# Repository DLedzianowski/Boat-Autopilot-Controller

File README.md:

# Boat-Autopilot-Controller
PCB for a small boat autopilot system. Collects sensor data and drives actuators to maintain set course/position.

## Main Features
- STM32WB55 – main MCU with BLE
- MAX-M10S – GNSS positioning
- TMC2208 – stepper motor driver
- LIS3MDL – magnetometer (compass)
- AS5600 connector – absolute encoder input
- DC motor controller connector

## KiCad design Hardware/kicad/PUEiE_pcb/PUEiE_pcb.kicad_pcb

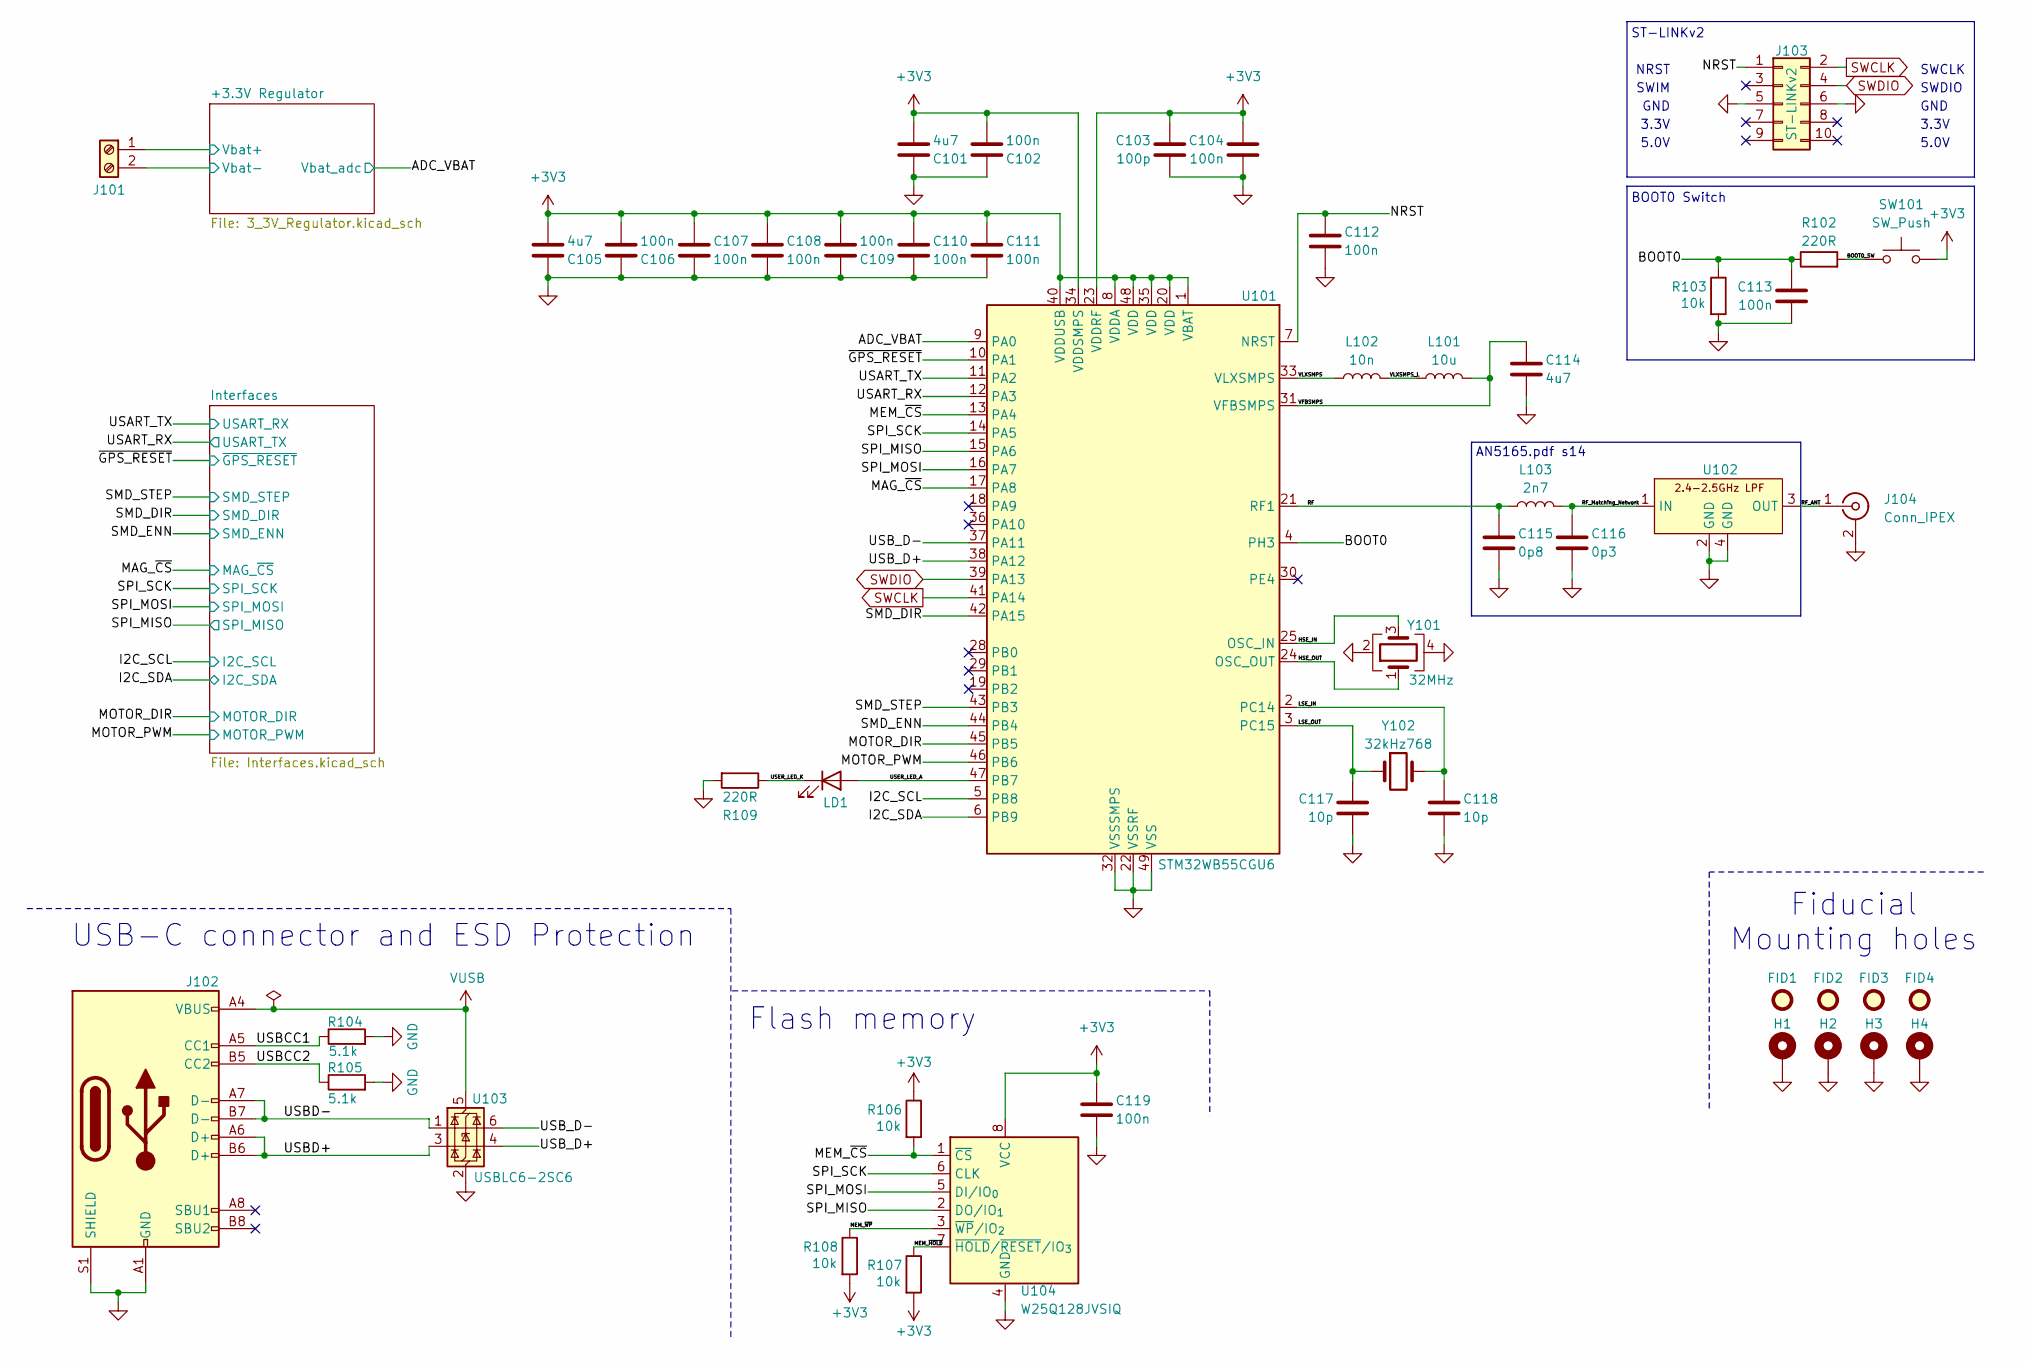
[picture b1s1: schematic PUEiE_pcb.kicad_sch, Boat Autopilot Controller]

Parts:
C101, C105, C114: 4u7; C_0805_2012Metric; MFR Part CL21A475KAQNNNE
C102, C104, C106, C107, C108, C109, C110, C111, C112, C113, C119: 100n; C_0805_2012Metric; MFR Part CL21B104KCFNNNE
C103: 100p; C_0805_2012Metric; MFR Part CL21C101JBANNNC
C115: 0p8; C_0402_1005Metric; MFR Part GRM1555C1HR80BA01D
C116: 0p3; C_0402_1005Metric; MFR Part GRM1555C1HR30WA01D
C117, C118: 10p; C_0603_1608Metric; MFR Part CL10C100JB8NNNC
FID1, FID2, FID3, FID4: Fiducial; Fiducial_1mm_Mask2mm
H1, H2, H3, H4: MountingHole_Pad; MountingHole_3.2mm_M3_Pad
J101: Screw_Terminal_01x02; TerminalBlock_Phoenix_PT-1,5-2-3.5-H_1x02_P3.50mm_Horizontal; MFR Part PRT-08084
J102: USB_C_Receptacle_USB2.0_16P; USB_C_Receptacle_GCT_USB4105-xx-A_16P_TopMnt_Horizontal; MFR Part USB4105-GF-A-060
J103: ST-LINKv2; PinHeader_2x05_P2.54mm_Vertical; MFR Part HX JN1.27-2x5P ZZ H4.9
J104: Conn_IPEX; IPEX Male; MFR Part BWIPX-1-001E
L101: 10u; L_0603_1608Metric; MFR Part SDFL1608S100KTF
L102: 10n; L_0402_1005Metric; MFR Part LQG15WZ10NJ02D
L103: 2n7; L_0402_1005Metric; MFR Part LQG15HS2N7S02D
LD1: LD1; LED_0805_2012Metric; MFR Part NCD0805B2
R102, R109: 220R; R_0805_2012Metric; MFR Part 0805W8F2200T5E
R103, R106, R107, R108: 10k; R_0805_2012Metric; MFR Part 0805W8F1002T5E
R104, R105: 5.1k; R_0805_2012Metric; MFR Part 0805W8F5101T5E
SW101: SW_Push; SW_2pin_5.5x2.0mm; MFR Part TS-1088-AR02016
U101: STM32WB55CGU6; QFN-48-1EP_7x7mm_P0.5mm_EP5.6x5.6mm_ThermalVias; MFR Part STM32WB55CGU6
U102: DLF162500LT-5028A1; MFR Part DLF162500LT-5028A1
U103: USBLC6-2SC6; SOT-23-6; MFR Part USBLC6-2SC6
U104: W25Q128JVSIQ; SOIC-8_5.3x5.3mm_P1.27mm; MFR Part W25Q128JVSIQ
Y101: 32MHz; Crystal_SMD_2016-4Pin_2.0x1.6mm; MFR Part NX2016SA-32MHZ-STD-CZS-5
Y102: 32kHz768; Crystal_SMD_2012-2Pin_2.0x1.2mm; MFR Part NX2012SA 32.768KHZ STD-MUB-1

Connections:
+3V3: C101.2, C102.2, C103.1, C104.1, C105.2, C106.2, C107.1, C108.1, C109.2, C110.1, C111.1, C119.1, R106.1, R107.2, R108.2, SW101.2, U101.1 (VBAT), U101.8 (VDDA), U101.20 (VDD), U101.23 (VDDRF), U101.34 (VDDSMPS), U101.35 (VDD), U101.40 (VDDUSB), U101.48 (VDD), U104.8 (VCC); also elsewhere on the board
/+3.3V Regulator/Vbat+: J101.1; also elsewhere on the board
/ADC_VBAT: U101.9 (PA0); also elsewhere on the board
/BOOT0: C113.1, R102.1, R103.1, U101.4 (PH3)
/BOOT0_SW: R102.2, SW101.1
/HSE_IN: U101.25 (OSC_IN), Y101.3
/HSE_OUT: U101.24 (OSC_OUT), Y101.1
/I2C_SCL: U101.5 (PB8); also elsewhere on the board
/I2C_SDA: U101.6 (PB9); also elsewhere on the board
/LSE_IN: C118.1, U101.2 (PC14), Y102.2
/LSE_OUT: C117.1, U101.3 (PC15), Y102.1
/MAG_~CS: U101.17 (PA8); also elsewhere on the board
/MEM_~CS: R106.2, U101.13 (PA4), U104.1 (~CS)
/MEM_~HOLD: R107.1, U104.7 (~HOLD/~RESET/IO_{3})
/MEM_~WP: R108.1, U104.3 (~WP/IO_{2})
/MOTOR_DIR: U101.45 (PB5); also elsewhere on the board
/MOTOR_PWM: U101.46 (PB6); also elsewhere on the board
/NRST: C112.1, J103.1, U101.7 (NRST)
/RF: C115.1, L103.1, U101.21 (RF1)
/RF_ANT: J104.1 (In), U102.3 (OUT)
/RF_Matching_Network: C116.1, L103.2, U102.1 (IN)
/SMD_DIR: U101.42 (PA15); also elsewhere on the board
/SMD_ENN: U101.44 (PB4); also elsewhere on the board
/SMD_STEP: U101.43 (PB3); also elsewhere on the board
/SPI_MISO: U101.15 (PA6), U104.2 (DO/IO_{1}); also elsewhere on the board
/SPI_MOSI: U101.16 (PA7), U104.5 (DI/IO_{0}); also elsewhere on the board
/SPI_SCK: U101.14 (PA5), U104.6 (CLK); also elsewhere on the board
/USART_RX: U101.12 (PA3); also elsewhere on the board
/USART_TX: U101.11 (PA2); also elsewhere on the board
/USBCC1: J102.A5 (CC1), R104.1
/USBCC2: J102.B5 (CC2), R105.1
/USBD+: J102.A6 (D+), J102.B6 (D+), U103.3 (I/O2)
/USBD-: J102.A7 (D-), J102.B7 (D-), U103.1 (I/O1)
/USB_D+: U101.38 (PA12), U103.4 (I/O2)
/USB_D-: U101.37 (PA11), U103.6 (I/O1)
/USER_LED_A: LD1.2 (A), U101.47 (PB7)
/USER_LED_K: LD1.1 (K), R109.1
/VFBSMPS: C114.1, L101.2, U101.31 (VFBSMPS)
/VLXSMPS: L102.1, U101.33 (VLXSMPS)
/VLXSMPS_L: L101.1, L102.2
/~GPS_RESET: U101.10 (PA1); also elsewhere on the board
GND: C101.1, C102.1, C103.2, C104.2, C105.1, C106.1, C107.2, C108.2, C109.1, C110.2, C111.2, C112.2, C113.2, C114.2, C115.2, C116.2, C117.2, C118.2, C119.2, H1.1, H2.1, H3.1, H4.1, J101.2, J102.A1 (GND), J102.A12 (GND), J102.B1 (GND), J102.B12 (GND), J102.S1 (SHIELD), J103.5, J103.6, J104.2 (Ext), R103.2, R104.2, R105.2, R109.2, U101.22 (VSSRF), U101.32 (VSSSMPS), U101.49 (VSS), U102.2 (GND), U102.4 (GND), U103.2 (GND), U104.4 (GND), Y101.2, Y101.4; also elsewhere on the board
SWCLK: J103.2, U101.41 (PA14)
SWDIO: J103.4, U101.39 (PA13)
VUSB: J102.A4 (VBUS), J102.A9 (VBUS), J102.B4 (VBUS), J102.B9 (VBUS), U103.5 (VBUS); also elsewhere on the board

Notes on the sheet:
AN5165.pdf s14
5.0V
BOOT0 Switch
GND
USB-C connector and ESD Protection
3.3V
SWDIO
SWCLK
ST-LINKv2
Fiducial Mounting holes
SWIM
Flash memory
NRST

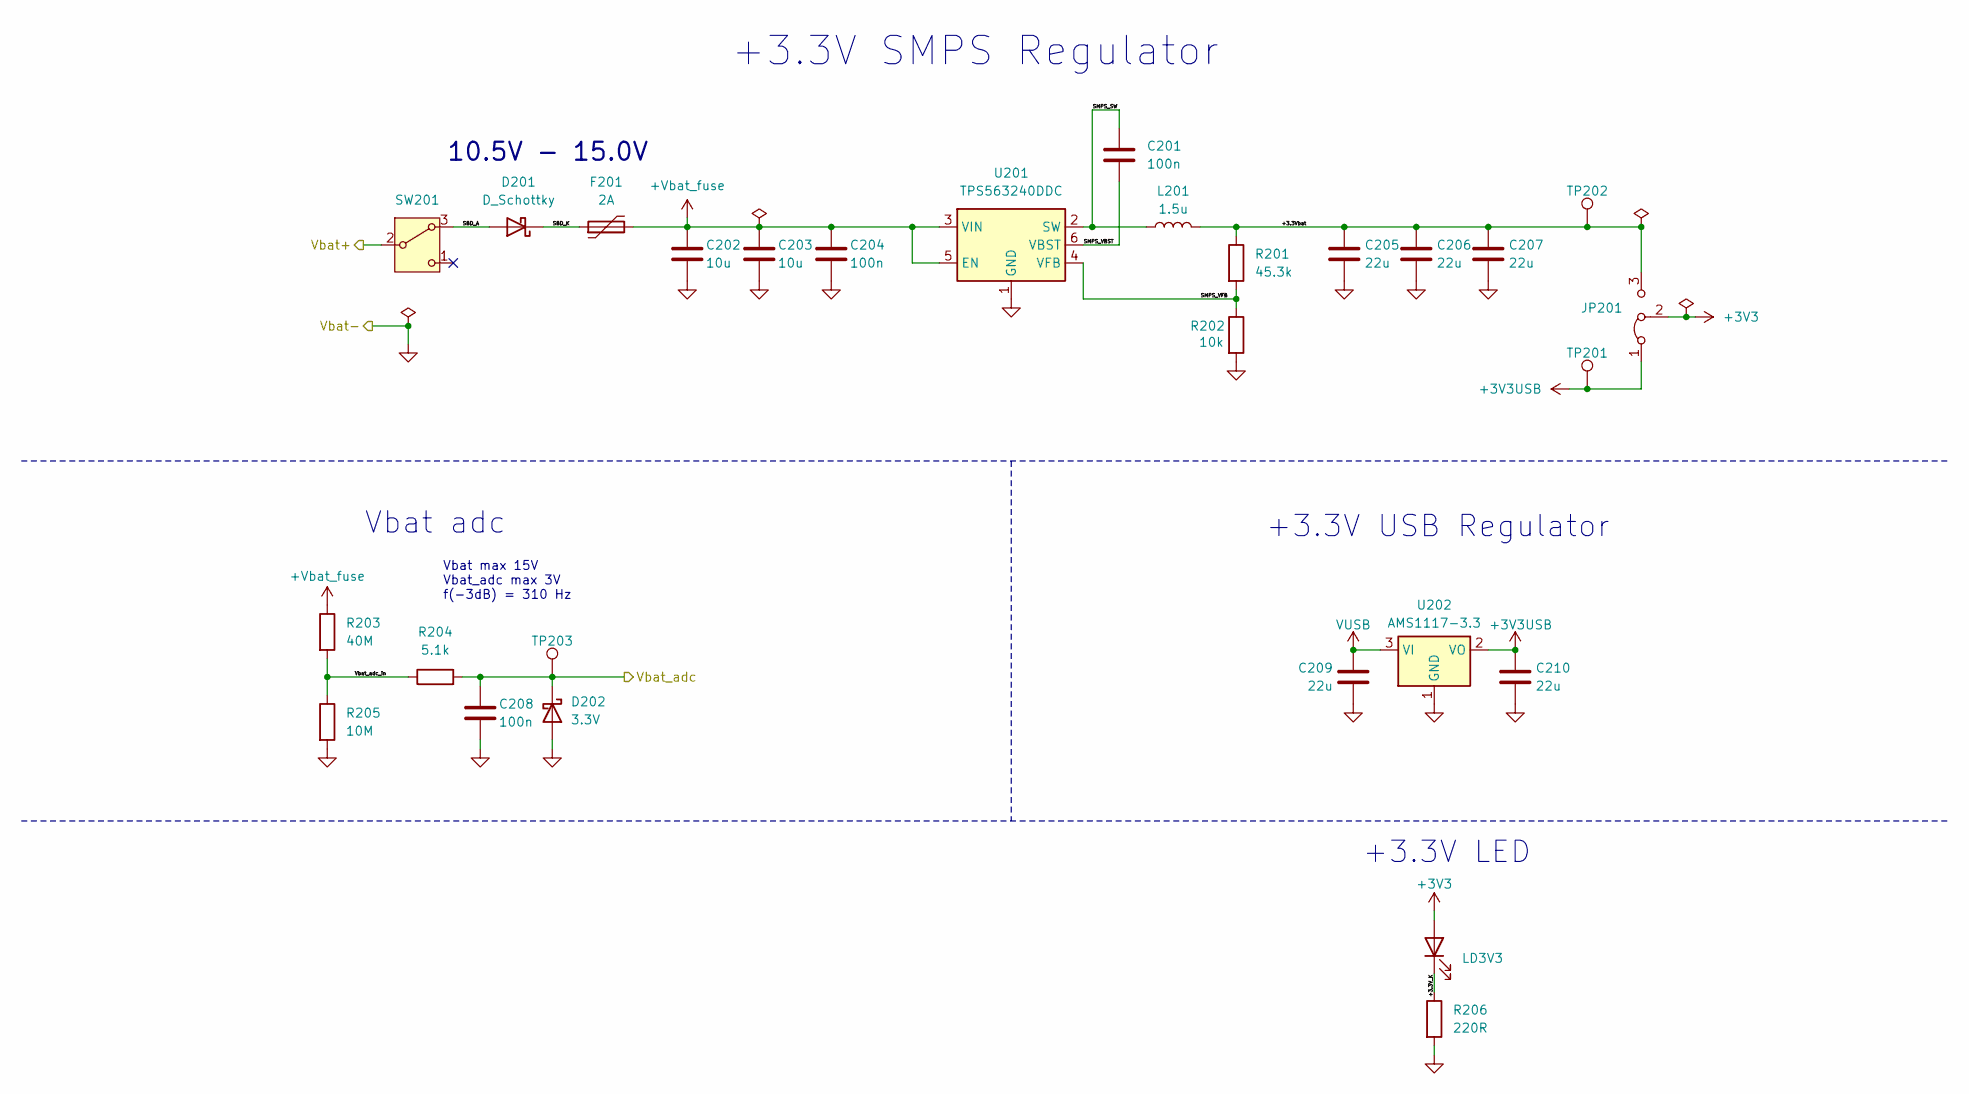
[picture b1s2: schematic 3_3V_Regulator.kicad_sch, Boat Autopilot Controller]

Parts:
C201: 100n; C_0603_1608Metric; MFR Part EMK107B7104KA-T
C202, C203: 10u; C_0805_2012Metric; MFR Part GRM21BR61E106MA73L
C204, C208: 100n; C_0805_2012Metric; MFR Part CL21B104KCFNNNE
C205, C206, C207, C209, C210: 22u; C_0603_1608Metric; MFR Part GRM188R60J226MEA0D
D201: D_Schottky; D_SMA; MFR Part SS34
D202: 3.3V; D_SOD-323; MFR Part MMSZ5226BS-7-F
F201: 2A; Fuseholder_Clip-5x20mm_Littelfuse_111_Inline_P20.00x5.00mm_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; MFR Part 5x20 环保 保险管夹/座
JP201: Jumper_3_Bridged12; PinHeader_1x03_P2.54mm_Vertical
L201: 1.5u; L_Sunlord_MWSA1005S; MFR Part 104CDMCCDS-1R5MC
LD3V3: +3.3V; LED_0805_2012Metric; MFR Part NCD0805R1
R201: 45.3k; R_0805_2012Metric; MFR Part 0805W8F4532T5E
R202: 10k; R_0805_2012Metric; MFR Part 0805W8F1002T5E
R203: 40M; R_0805_2012Metric; MFR Part RH73H2A40MKTN
R204: 5.1k; R_0805_2012Metric; MFR Part 0805W8F5101T5E
R205: 10M; R_0805_2012Metric; MFR Part 0805W8F1005T5E
R206: 220R; R_0805_2012Metric; MFR Part 0805W8F2200T5E
SW201: SW_Nidec_CAS-120A1; PinHeader_1x03_P2.54mm_Vertical; MFR Part TS01CBE
TP201, TP202, TP203: TestPoint; TestPoint_Pad_D2.0mm
U201: TPS563240DDC; SOT-23-6; MFR Part TPS563240DDCR
U202: AMS1117-3.3; SOT-223-3_TabPin2; MFR Part AMS1117-3.3

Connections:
+3V3: JP201.2 (C), LD3V3.2 (A); also elsewhere on the board
+3V3USB: C210.1, JP201.1 (A), TP201.1, U202.2 (VO)
+Vbat_fuse: C202.1, C203.1, C204.1, F201.2, R203.1, U201.3 (VIN), U201.5 (EN); also elsewhere on the board
/+3.3V Regulator/+3.3V_K: LD3V3.1 (K), R206.1
/+3.3V Regulator/+3.3Vbat: C205.1, C206.1, C207.1, JP201.3 (B), L201.2, R201.1, TP202.1
/+3.3V Regulator/SBD_A: D201.2 (A), SW201.3 (A)
/+3.3V Regulator/SBD_K: D201.1 (K), F201.1
/+3.3V Regulator/SMPS_SW: C201.1, L201.1, U201.2 (SW)
/+3.3V Regulator/SMPS_VBST: C201.2, U201.6 (VBST)
/+3.3V Regulator/SMPS_VFB: R201.2, R202.1, U201.4 (VFB)
/+3.3V Regulator/Vbat+: SW201.2 (B); also elsewhere on the board
/+3.3V Regulator/Vbat_adc_in: R203.2, R204.1, R205.1
/ADC_VBAT: C208.1, D202.1 (K), R204.2, TP203.1; also elsewhere on the board
GND: C202.2, C203.2, C204.2, C205.2, C206.2, C207.2, C208.2, C209.2, C210.2, D202.2 (A), R202.2, R205.2, R206.2, U201.1 (GND), U202.1 (GND); also elsewhere on the board
VUSB: C209.1, U202.3 (VI); also elsewhere on the board

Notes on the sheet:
Vbat adc
+3.3V SMPS Regulator
Vbat max 15V Vbat_adc max 3V f(-3dB) = 310 Hz
+3.3V USB Regulator
+3.3V LED
10.5V - 15.0V

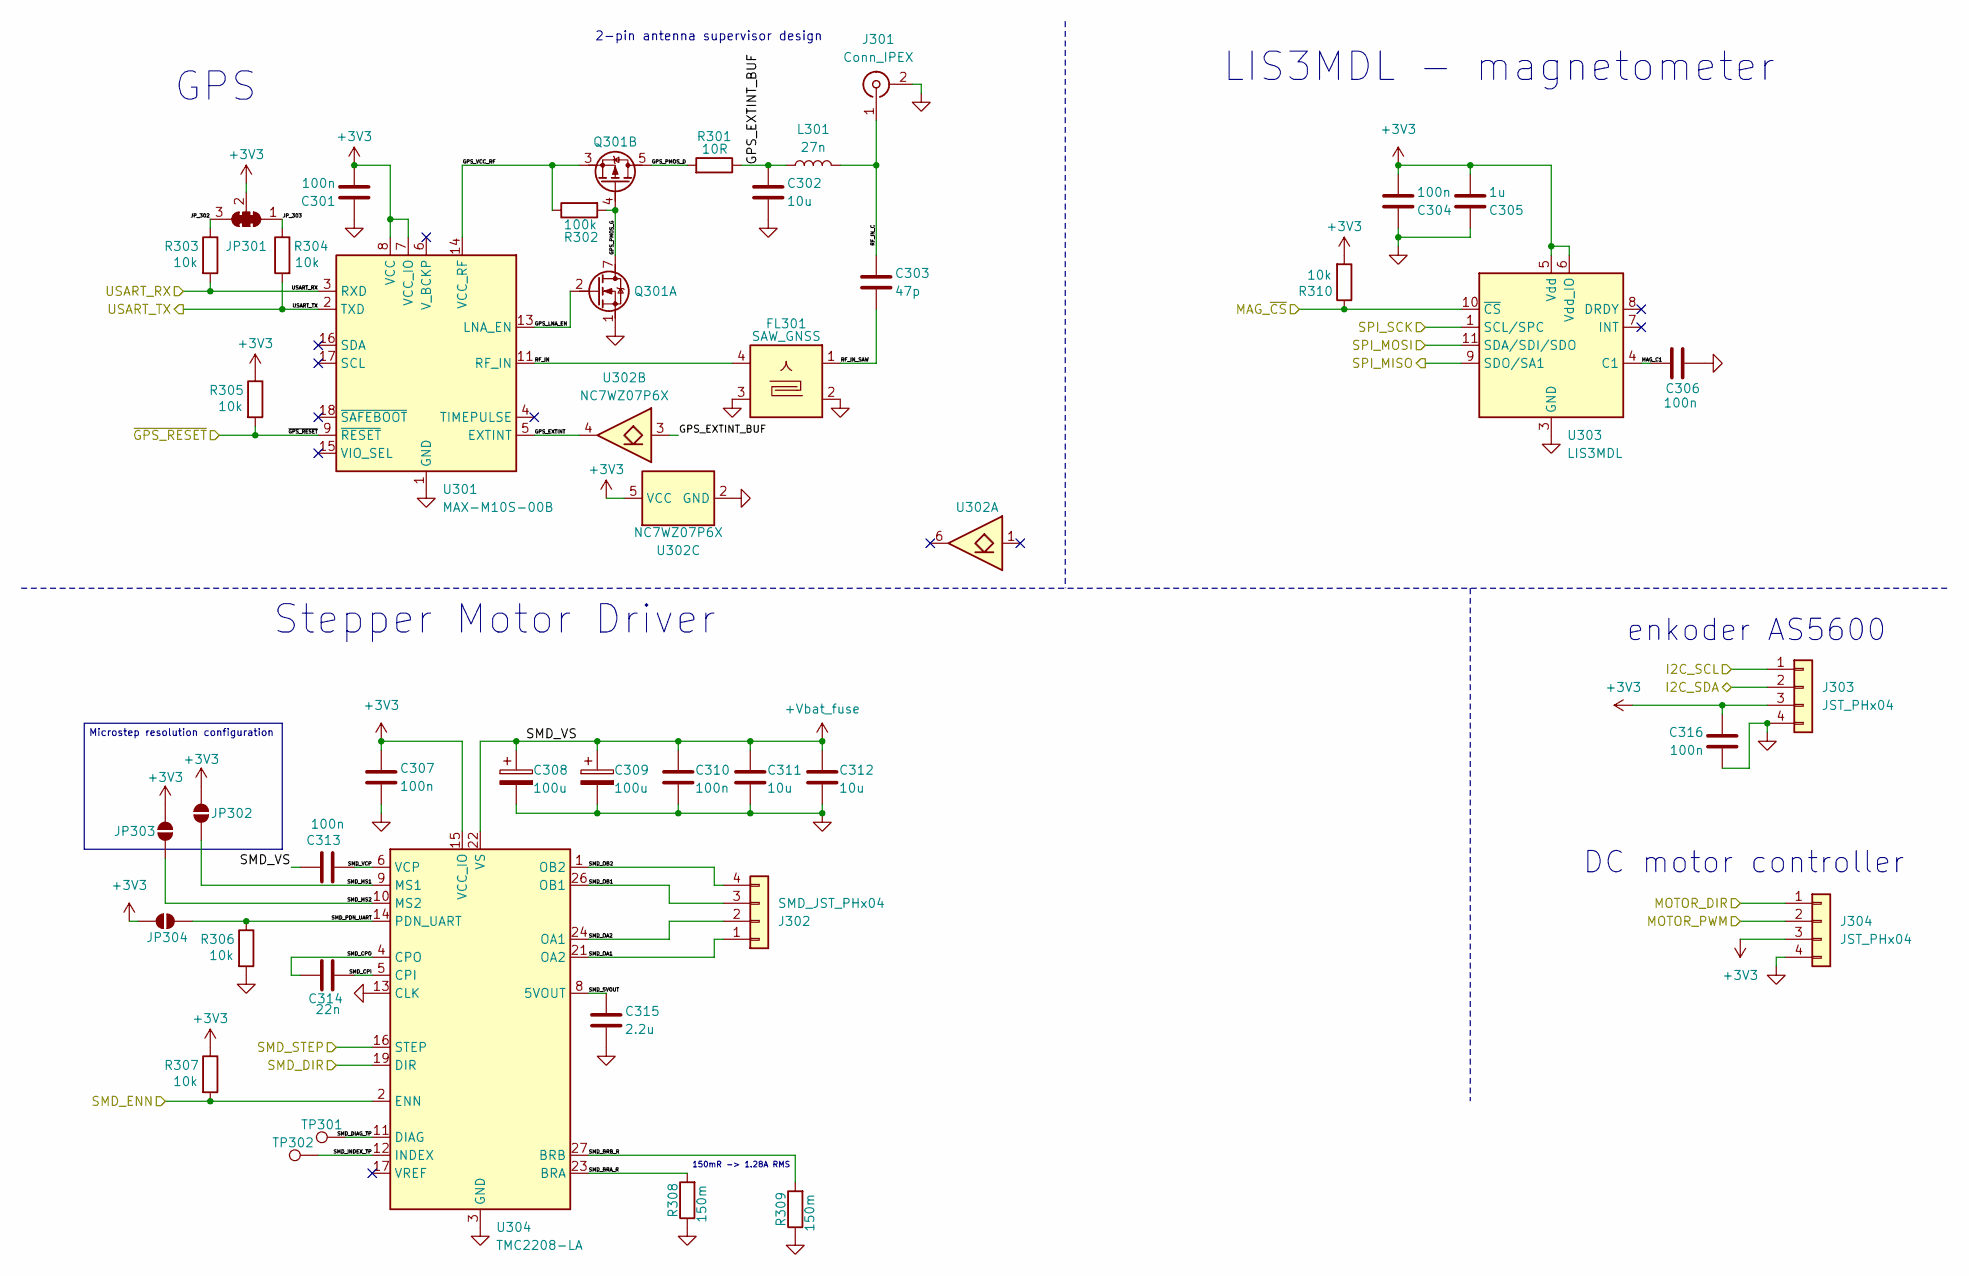
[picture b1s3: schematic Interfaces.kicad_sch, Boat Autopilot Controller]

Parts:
C301, C304, C306, C307, C310, C313, C316: 100n; C_0805_2012Metric; MFR Part CL21B104KCFNNNE
C302: 10u; C_0805_2012Metric; MFR Part CL21B103KBANNNC
C303: 47p; C_0805_2012Metric; MFR Part C2012C0G1H470JT000N
C305: 1u; C_0805_2012Metric; MFR Part CL21B105KBFNNNE
C308, C309: 100u; CP_Elec_6.3x7.7; MFR Part RVT1E101M0607
C311, C312: 10u; C_1206_3216Metric; MFR Part CL31A106KBHNNNE
C314: 22n; C_0805_2012Metric; MFR Part CL21B104KCFNNNE
C315: 2.2u; C_0805_2012Metric; MFR Part CL21A225KBQNNNE
FL301: SAW_GNSS; Filter_1109-5_1.1x0.9mm; MFR Part SAFFB1G56KB0F0AR1X
J301: Conn_IPEX; IPEX Male; MFR Part BWIPX-1-001E
J302: SMD_JST_PHx04; JST_XH_S4B-XH-A_1x04_P2.50mm_Horizontal; MFR Part S4B-XH-A-1
J303, J304: JST_PHx04; JST_XH_S4B-XH-A_1x04_P2.50mm_Horizontal; MFR Part S4B-XH-A-1
JP301: SolderJumper_3_Bridged123; SolderJumper-3_P2.0mm_Open_TrianglePad1.0x1.5mm
JP302, JP303, JP304: SolderJumper_2_Open; SolderJumper-2_P1.3mm_Open_TrianglePad1.0x1.5mm
L301: 27n; L_0402_1005Metric; MFR Part LQG15HS27NJ02D
Q301: ZXMC4559DN8TA; SOP-8_3.76x4.96mm_P1.27mm; MFR Part ZXMC4559DN8TA
R301: 10R; R_0603_1608Metric; MFR Part ERJUP3J100V
R302: 100k; R_0603_1608Metric; MFR Part 0603WAF1003T5E
R303, R304, R305, R306, R307, R310: 10k; R_0805_2012Metric; MFR Part 0805W8F1002T5E
R308, R309: 150m; R_1206_3216Metric; MFR Part 1206W4F150LT5E
TP301, TP302: TestPoint; TestPoint_Pad_D2.0mm
U301: MAX-M10S-00B; ublox_MAX; MFR Part MAX-M10S-00B
U302: NC7WZ07P6X; SOT-363_SC-70-6; MFR Part NC7WZ07P6X
U303: LIS3MDL; LGA-12_2x2mm_P0.5mm; MFR Part LIS3MDLTR
U304: TMC2208-LA; QFN-28-1EP_5x5mm_P0.5mm_EP3.75x3.75mm_ThermalVias; MFR Part TMC2208-LA-T

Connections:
+3V3: C301.2, C304.2, C305.2, C307.1, C316.1, J303.3, J304.3, JP301.2 (C), JP302.1 (A), JP303.1 (A), JP304.2 (B), R305.1, R307.1, R310.2, U301.7 (VCC_IO), U301.8 (VCC), U302.5 (VCC), U303.5 (Vdd), U303.6 (Vdd_IO), U304.15 (VCC_IO); also elsewhere on the board
+Vbat_fuse: C308.1, C309.1, C310.1, C311.1, C312.1, C313.1, U304.22 (VS), U304.28 (VS); also elsewhere on the board
/I2C_SCL: J303.1; also elsewhere on the board
/I2C_SDA: J303.2; also elsewhere on the board
/Interfaces/GPS_EXTINT: U301.5 (EXTINT), U302.4
/Interfaces/GPS_EXTINT_BUF: C302.1, L301.1, R301.1, U302.3
/Interfaces/GPS_LNA_EN: Q301.2 (G1), U301.13 (LNA_EN)
/Interfaces/GPS_PMOS_D: Q301.5 (D2), Q301.6 (D1), R301.2
/Interfaces/GPS_PMOS_G: Q301.4 (G2), Q301.7 (D1), Q301.8 (D1), R302.2
/Interfaces/GPS_VCC_RF: Q301.3 (S2), R302.1, U301.14 (VCC_RF)
/Interfaces/JP_302: JP301.3 (B), R303.1
/Interfaces/JP_303: JP301.1 (A), R304.1
/Interfaces/MAG_C1: C306.2, U303.4 (C1)
/Interfaces/RF_IN: FL301.4, U301.11 (RF_IN)
/Interfaces/RF_IN_C: C303.1, J301.1 (In), L301.2
/Interfaces/RF_IN_SAW: C303.2, FL301.1
/Interfaces/SMD_5VOUT: C315.1, U304.8 (5VOUT)
/Interfaces/SMD_BRA_R: R308.2, U304.23 (BRA)
/Interfaces/SMD_BRB_R: R309.2, U304.27 (BRB)
/Interfaces/SMD_CPI: C314.1, U304.5 (CPI)
/Interfaces/SMD_CPO: C314.2, U304.4 (CPO)
/Interfaces/SMD_DIAG_TP: TP301.1, U304.11 (DIAG)
/Interfaces/SMD_INDEX_TP: TP302.1, U304.12 (INDEX)
/Interfaces/SMD_MS1: JP302.2 (B), U304.9 (MS1)
/Interfaces/SMD_MS2: JP303.2 (B), U304.10 (MS2)
/Interfaces/SMD_OA1: J302.1, U304.21 (OA2)
/Interfaces/SMD_OA2: J302.2, U304.24 (OA1)
/Interfaces/SMD_OB1: J302.3, U304.26 (OB1)
/Interfaces/SMD_OB2: J302.4, U304.1 (OB2)
/Interfaces/SMD_PDN_UART: JP304.1 (A), R306.1, U304.14 (PDN_UART)
/Interfaces/SMD_VCP: C313.2, U304.6 (VCP)
/MAG_~CS: R310.1, U303.10 (~CS); also elsewhere on the board
/MOTOR_DIR: J304.1; also elsewhere on the board
/MOTOR_PWM: J304.2; also elsewhere on the board
/SMD_DIR: U304.19 (DIR); also elsewhere on the board
/SMD_ENN: R307.2, U304.2 (ENN); also elsewhere on the board
/SMD_STEP: U304.16 (STEP); also elsewhere on the board
/SPI_MISO: U303.9 (SDO/SA1); also elsewhere on the board
/SPI_MOSI: U303.11 (SDA/SDI/SDO); also elsewhere on the board
/SPI_SCK: U303.1 (SCL/SPC); also elsewhere on the board
/USART_RX: R304.2, U301.2 (TXD); also elsewhere on the board
/USART_TX: R303.2, U301.3 (RXD); also elsewhere on the board
/~GPS_RESET: R305.2, U301.9 (~RESET); also elsewhere on the board
GND: C301.1, C302.2, C304.1, C305.1, C306.1, C307.2, C308.2, C309.2, C310.2, C311.2, C312.2, C315.2, C316.2, FL301.2, FL301.3, FL301.5, J301.2 (Ext), J303.4, J304.4, Q301.1 (S1), R306.2, R308.1, R309.1, U301.1 (GND), U301.10 (GND), U301.12 (GND), U302.2 (GND), U303.2 (GND), U303.3 (GND), U303.12 (GND), U304.3 (GND), U304.13 (CLK), U304.18 (GND), U304.29 (GND); also elsewhere on the board

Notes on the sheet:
GPS
enkoder AS5600
2-pin antenna supervisor design
DC motor controller
Stepper Motor Driver
LIS3MDL - magnetometer
Microstep resolution configuration
150mR -> 1.28A RMS

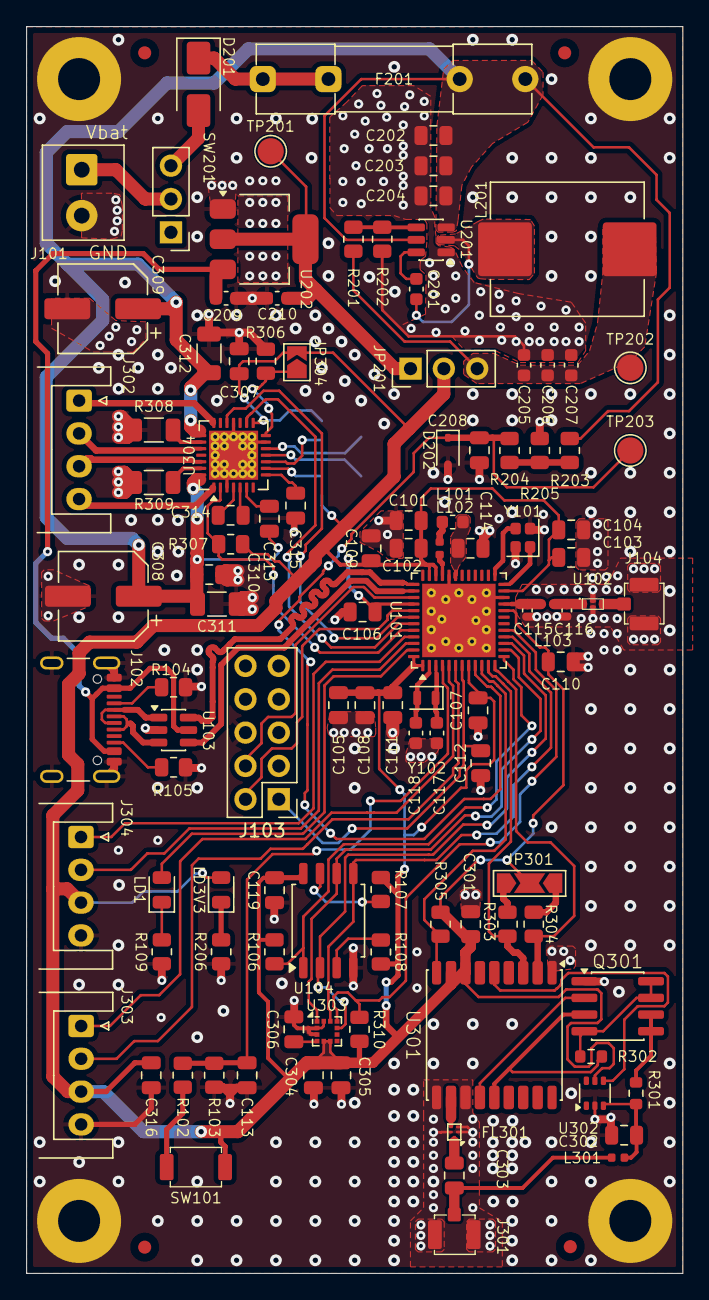
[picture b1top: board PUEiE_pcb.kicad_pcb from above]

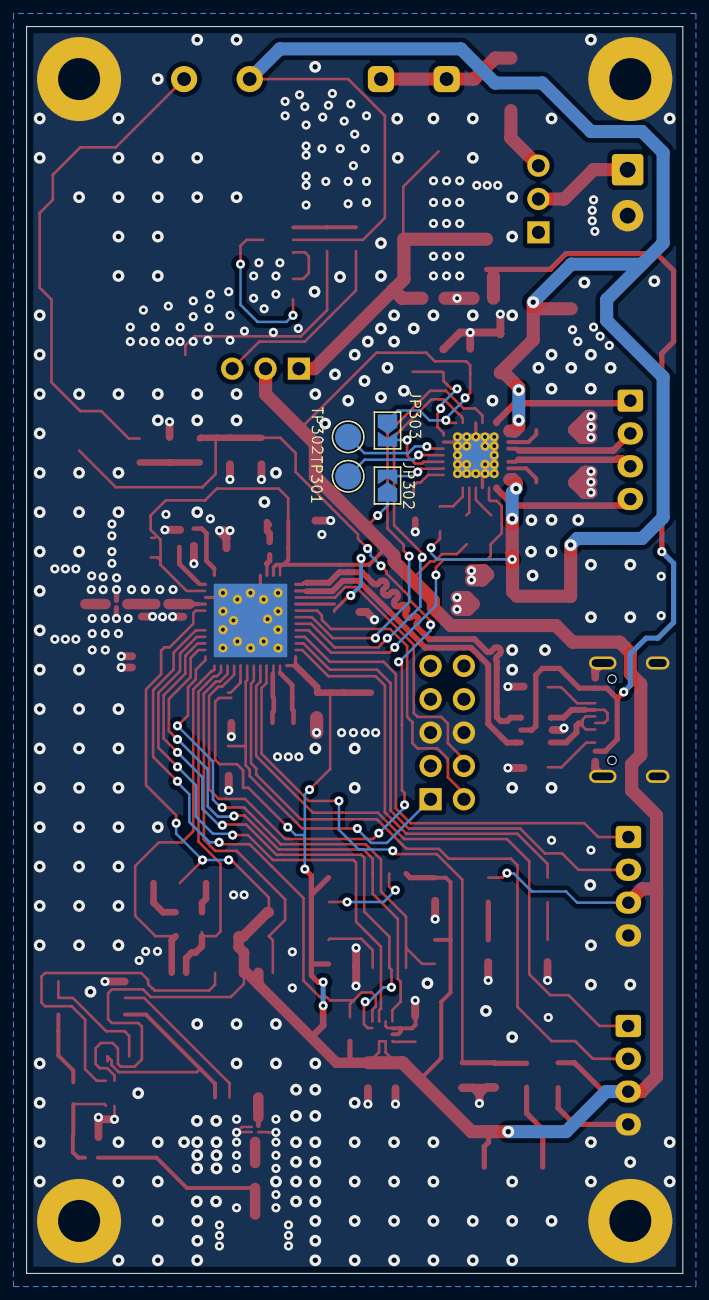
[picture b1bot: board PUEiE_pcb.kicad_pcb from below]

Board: 2 copper layers, 50.0 x 95.0 mm, 121 parts (4 on the bottom side), 82 nets.

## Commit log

2025-10-28 tps563240, GNSS
2025-10-30 usbc
2025-10-30 cleanup
2025-11-04 Vbat
2025-11-04 magnetometer ,stepper controller
2025-11-06 stm32WB55
2025-11-11 stm32WB
2025-11-15 All Schematics
2025-11-16 Board Setup
2025-11-18 pcb placement
2025-11-21 PCB layout
2025-11-22 Final PCB layout
2025-12-09 Final PCB design
